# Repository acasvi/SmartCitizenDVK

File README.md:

Smart Citizen Kit DVK
=====================

**[Smart Citizen Kit](https://github.com/fablabbcn/Smart-Citizen-Kit) Develoment Kit (DVK) for [RTX4100](http://www.rtx.dk/RTX41xx_Wi-Fi_modules-3921.aspx) and [Arduino Due](http://arduino.cc/en/Main/arduinoBoardDue)**

*The Smart Citizen DVK is an Arduino Shield for the Arduino DUE and the upcoming Arduino Zero aimed to help developers prototype applications for the new Smart Citizen Kit Data Board 2.0. It contains a RTX4100 low-power Wi-Fi module, an SD card socket and a digital temperature and humidity sensor.*

## First Steps

### Installing the toolchain

The tool chain includes primarily a pre-processor, a compiler, and a linker. The RTX41xx relies on the GCC ARM Embedded tool chain from ARM.

Prior to installation, download the GNU tools for ARM embedded processors installation file from: https://launchpad.net/gcc-arm-embedded/+milestone/4.7-2013-q3-update

Download the `gcc-arm-none-eabi-4_7-2013q3-20130916-win32.exe` file, save to disk and run the `.exe` file. 

Don't forget to click “Add path to environment variable” checkbox at the end of the installation.

Refer to **[RTX4100_User_Guide_Tools_Installation_UG2.pdf](https://github.com/fablabbcn/SmartCitizenDVK/blob/master/Documentation/RTX4100/RTX4100_User_Guide_Tools_Installation_UG2.pdf)** for a further explanation about installation the toolchain and SDK.

### Installing the SDK

After installing the Tool Chain, it is time to install the RTX41xx Software Development Kit (SDK). 

Go to the following link: [www.rtx.dk/LPW/RTX4100](http://www.rtx.dk/LPW/RTX4100) and click on **DOWNLOAD** link on top right.

You have to sign up to download the latest SDK `AmelieSdk_v1.6.0.58.exe`.

Once you have downloaded open the `.exe` to start the installer.

The SDK download from RTX includes the following items:

* Sample code implementing the following applications: 
    * Blinky: Small example application that uses a timer to flash a LED on the demo board.
    * TCP Server/client
    * UDP Server/client
    * Terminal Application
    * 3 different Temperature Sensor implementations, demonstrating various low power capabilities.
    * TempSensorSoftApCfg, demonstrating how it is possible to configure a module by booting it in SoftAP mode with telnet support.
    * SoftApTcpServer, demonstrating an AP implementation with TCP server.
    * WebServer, demonstrating a very simple WEB server implementation.
    * Tcp2Uart, demonstrates a simple implementation of a data pipe
    * Cloud reference applications, demonstrating various cloud solutions 
    * Header files for available APIs.
    * Build environment: Build scripts, linker files etc. are provided for ARM GCC Em-bedded tool chain.
    * RTX EAI Port Server: PC application used for communicating with the hardware.
    * CoLA Controller DLL: Used for selecting active image and updating firmware.
    * CoLA Controller GUI: Example application using the DLL. In the end product the DLL could be used directly from e.g. an Eclipse IDE.

It is assumed that the SDK has been installed in c:\AmelieSdk\vX.XX, and the following description of the folder structure is relative to this location.

The following folders are at top level: 

* **3Party** – includes source files from 3rd parties. The most important file found here is the “efm32lib” from Energy Micro which is used to access the peripherals of the MCU.
* **ColaController** – The PC tool used to download Co-Located Applications to the module via the UART.
* **Components** – Source code to some common components used when the CoLA is built.
* **Documents** – Documentation folder.
* **Include** – Common header files.
* **Projects** – This is where you find the reference CoLA applications
* **Tools** – A set of tools used when the CoLA is built. This also includes the RtxBuild system used for the build process.

In the Project folder (Projects\Amelie\COLApps) you find the following folders:

* **Apps** – A set of reference applications 
	* Blinky – The source code for the Blinky application
	* Blinky/Build/RTX4100_WSAB – Build folder for RTX4100 module on WSAB.
	* Blinky/Build/RTX4140_WSAB – Build folder for RTX4140 module on WSAB.
* **Config** – This folder holds various configuration header files required to build the reference applications.
* **Rsx** – PC tool for API mail trace via UART.
* **Scripts** – build/linker scripts.

In the Components folder (Projects\Amelie\Componets) you find the following folders: 

* **Api** – Some API header files
* **ApiMps** – API mail packing and sending helper functions
* **Drivers** – Implementation of various hardware drivers 
* **PtApps** – Protothread based application framework used by all reference applica-tions except Blinky. 

Refer to **[RTX4100_User_Guide_Tools_Installation_UG2.pdf](https://github.com/fablabbcn/SmartCitizenDVK/blob/master/Documentation/RTX4100/RTX4100_User_Guide_Tools_Installation_UG2.pdf)** for a further explanation about installation the toolchain and SDK.

#### Application Development

For start with the **application development** refer to chapter 4 on [RTX4100_User_Guide_Application_Development_UG3.pdf](https://github.com/fablabbcn/SmartCitizenDVK/blob/master/Documentation/RTX4100/RTX4100_User_Guide_Application_Development_UG3.pdf)

For **terminal commands to configure WIFI** module refer to chapter 5 on [RTX4100_User_Guide_Module_Evaluation_UG1.pdf](https://github.com/fablabbcn/SmartCitizenDVK/blob/master/Documentation/RTX4100/RTX4100_User_Guide_Application_Development_UG3.pdf)

For **API used to program Co-Located Applications (CoLA)** on top of the Amelie Wi-Fi platform refer to [AmelieApi_V0106_N0052.pdf](https://github.com/fablabbcn/SmartCitizenDVK/blob/master/Documentation/RTX4100/AmelieApi_V0106_N0052.pdf)

## Software

All the boards come with:

* Arduino firmware *[SmartCitizen_DVK.ino](https://github.com/fablabbcn/SmartCitizenDVK/tree/master/Firmware)* uploaded. 
* RTX firmware uploaded
* CoLA application for terminal communication with WIFI module uploaded, for available **terminal commands** refer to chapter 5 on *[RTX4100_User_Guide_Module_Evaluation_UG1.pdf](https://github.com/fablabbcn/SmartCitizenDVK/blob/master/Documentation/RTX4100/RTX4100_User_Guide_Module_Evaluation_UG1.pdf)*

To use the RTX Shield connect an usb cable in the programming port of the Arduino Due, the one closest to the DC power jack.

As you can see, the RTX shield has two push buttons, **S1** and **S2**. With this two buttons you can change between 4 modes of operation:

####MODE 1

This is the default mode when you connect the board, green LED is ON. This mode sendsthrough USB-Serial, at 9600 bauds, the values captured by the temperature and humidity sensors and tells you if a SD Card is detected or not. You can find this values in the `main()` function of `SmartCitizen_DVK.ino`.

####MODE 2

If **S1** button is pushed, the green LED starts to blinking. You are on terminal mode. If a CoLa app for terminal communication is uploaded, yelllow LED ON, you can talk through USB-serial with the RTX WIFI module. If you push again S1, you'll go back to **MODE 1**.

####MODE 3

If **S2** button is pushed ,the blue LED goes ON, you can now upload CoLA applications with **ColaController**, the PC tool used to download Co-Located Applications to the module via the UART. You can find this tool on **ColaController** folder inside **Amelie SDK** folder.

####MODE 4

If **S2** button is pushed again, the green and blue LEDs goes ON, you will enter in RTX firmware uploading mode and the blue LED will start blinking.

To perform the Firmware update:

1. Download the firmware file **RTX41xx_Platform_Firmware_Update_Pack_v1.6.0.52.zip** from the RTX [download center](http://www.rtx.dk/Download_Center_Login-3980.aspx). 
2. Unzip the file to your harddrive. As this document is included in the above ZIP file you have probably already downloaded the file.

*NOTE: Each time you plug the arduino due with the shield to your computer automatically reses the mode to mode 1.*

### Existing software

* [Smart Citizen Kit firmware](https://github.com/fablabbcn/Smart-Citizen-Kit) for the Ambient Sensor Board 1.0-1.2 *(MCU ATMEGA32U4)*
* [Smart Citizen Kit RTX4100 Application - BETA](https://github.com/fablabbcn/SmartCitizenRTX4100)

## Hardware

SmartCitizen DVK shield design files are available [here](https://github.com/fablabbcn/SmartCitizenDVK/hardware).

### RTX4100 - Low power wifi module

* [http://www.rtx.dk/RTX41xx_Wi-Fi_modules-3921.aspx](http://www.rtx.dk/RTX41xx_Wi-Fi_modules-3921.aspx)

* [http://www.rtx.dk/Wi-Fi_Documentation-4028.aspx](http://www.rtx.dk/Wi-Fi_Documentation-4028.aspx)

The RTX41xx Wi-Fi Module is a low power solution, which is achieved through the use of the  Energy Micro Gecko and Atheros AR4100 Wi-Fi SiP.

**The I/O's include:**

* Power supply pins
* ADC ports, DAC ports
* GPIO ports
* UART, SPI, I2C
* Timers

#### NC7SZ157P6X – MUX

[http://www.mouser.com/ds/2/149/NC7SZ157-96268.pdf](http://www.mouser.com/ds/2/149/NC7SZ157-96268.pdf)

The mux is used to select from Arduino which serial port of the RTX4100 you want to use.

You can select between two serial ports:

* **LEU1**: (LEUART) is used for the Terminal application (such at Putty), for example.
* **US1**: (USART) is used for the COLApp loading, SW debugging and Platform updates (using the COLApp Controller)

#### MCP1725-3002E/SN LDO REGULATOR

[http://ww1.microchip.com/downloads/en/DeviceDoc/22026b.pdf](%22http:)

3V fixed voltage regulator

#### CD74HC4050M High-to-Low Voltage Level Converter

[http://www.mouser.com/ds/2/405/schs205i-101882.pdf](http://www.mouser.com/ds/2/405/schs205i-101882.p)

IC used as logic level converter between Arduino and the RTX4100 module.

#### SDCARD

[http://www.mouser.com/ds/2/185/e60900232-38395.pdf](http://www.mouser.com/ds/2/185/e60900232-38395.pdf)

To hold the SD card we are using the DM3CS holder. The SD card is powered at 3V and communicates with the RTX4100 through SPI protocol.

#### SHT21 Humidity and Temperature Sensor IC

[http://www.sensirion.com/fileadmin/user_upload/customers/sensirion/Dokumente/Humidity/Sensirion_Humidity_SHT21_Datasheet_V4.pdf](http://www.sensirion.com/fileadmin/user_upload/customers/s)

#### LEDs

* **LED1 YELLOW:** Connected to RTX4100 pin 27, for testing Blink CoLA example
* **LED2 BLUE:** Connected to Arduino Analog0 pin
* **LED3 GREEN:** Connected to Arduino Analog1 pin

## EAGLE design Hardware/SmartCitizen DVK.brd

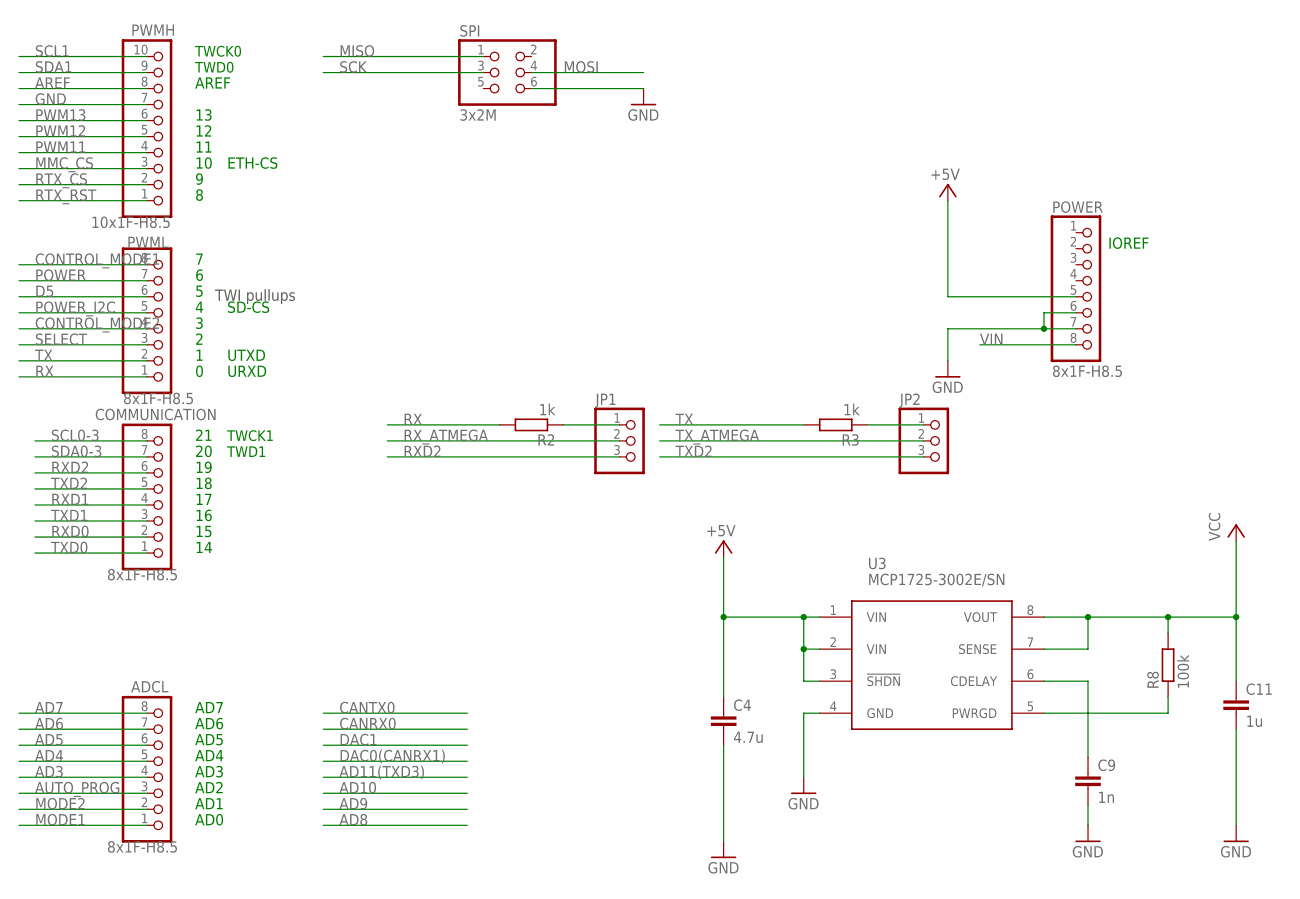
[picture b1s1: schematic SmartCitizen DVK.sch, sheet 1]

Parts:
ADCL: 8x1F-H8.5; 1X08
C4: 4.7u; C0805
C9: 1n; C0805
C11: 1u; C0805
COMMUNICATION: 8x1F-H8.5; 1X08
JP1, JP2: PINHD-1X3; 1X03
POWER: 8x1F-H8.5; 1X08
PWMH: 10x1F-H8.5; 1X10
PWML: 8x1F-H8.5; 1X08
R2, R3: 1k; R0805
R8: 100k; R0805
SPI: 3x2M; 2X03
U3: MCP1725-3002E/SN; SOIC8

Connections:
+5V: C4.1, POWER.5, U3.1 (VIN), U3.2 (VIN), U3.3 (!SHDN); also elsewhere on the board
AD3: ADCL.4
AD4: ADCL.5
AD5: ADCL.6
AD6: ADCL.7
AD7: ADCL.8
AREF: PWMH.8
AUTO_PROG: ADCL.3; also elsewhere on the board
CONTROL_MODE1: PWML.8; also elsewhere on the board
CONTROL_MODE2: PWML.4; also elsewhere on the board
D5: PWML.6
GND: C4.2, C9.2, C11.2, POWER.6, POWER.7, PWMH.7, SPI.6, U3.4 (GND); also elsewhere on the board
MISO: SPI.1; also elsewhere on the board
MMC_CS: PWMH.3; also elsewhere on the board
MODE1: ADCL.1; also elsewhere on the board
MODE2: ADCL.2; also elsewhere on the board
MOSI: SPI.4; also elsewhere on the board
unnamed: JP1.1, R2.1
unnamed: JP2.1, R3.1
unnamed: C9.1, U3.6 (CDELAY)
unnamed: R8.1, U3.5 (PWRGD)
POWER: PWML.7; also elsewhere on the board
POWER_I2C: PWML.5; also elsewhere on the board
PWM11: PWMH.4
PWM12: PWMH.5
PWM13: PWMH.6
RTX_CS: PWMH.2; also elsewhere on the board
RTX_RST: PWMH.1; also elsewhere on the board
RX: PWML.1, R2.2
RXD0: COMMUNICATION.2
RXD1: COMMUNICATION.4
RXD2: COMMUNICATION.6, JP1.3
RX_ATMEGA: JP1.2; also elsewhere on the board
SCK: SPI.3; also elsewhere on the board
SCL0-3: COMMUNICATION.8
SCL1: PWMH.10; also elsewhere on the board
SDA0-3: COMMUNICATION.7
SDA1: PWMH.9; also elsewhere on the board
SELECT: PWML.3; also elsewhere on the board
TX: PWML.2, R3.2
TXD0: COMMUNICATION.1
TXD1: COMMUNICATION.3
TXD2: COMMUNICATION.5, JP2.3
TX_ATMEGA: JP2.2; also elsewhere on the board
VCC: C11.1, R8.2, U3.7 (SENSE), U3.8 (VOUT); also elsewhere on the board
VIN: POWER.8

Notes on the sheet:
TWI pullups
TWCK1
TWD1
IOREF
TWCK0
TWD0
AD1
AD2
AD3
AD4
AD5
AD6
AD0
AREF
AD7
SD-CS
UTXD
URXD
ETH-CS

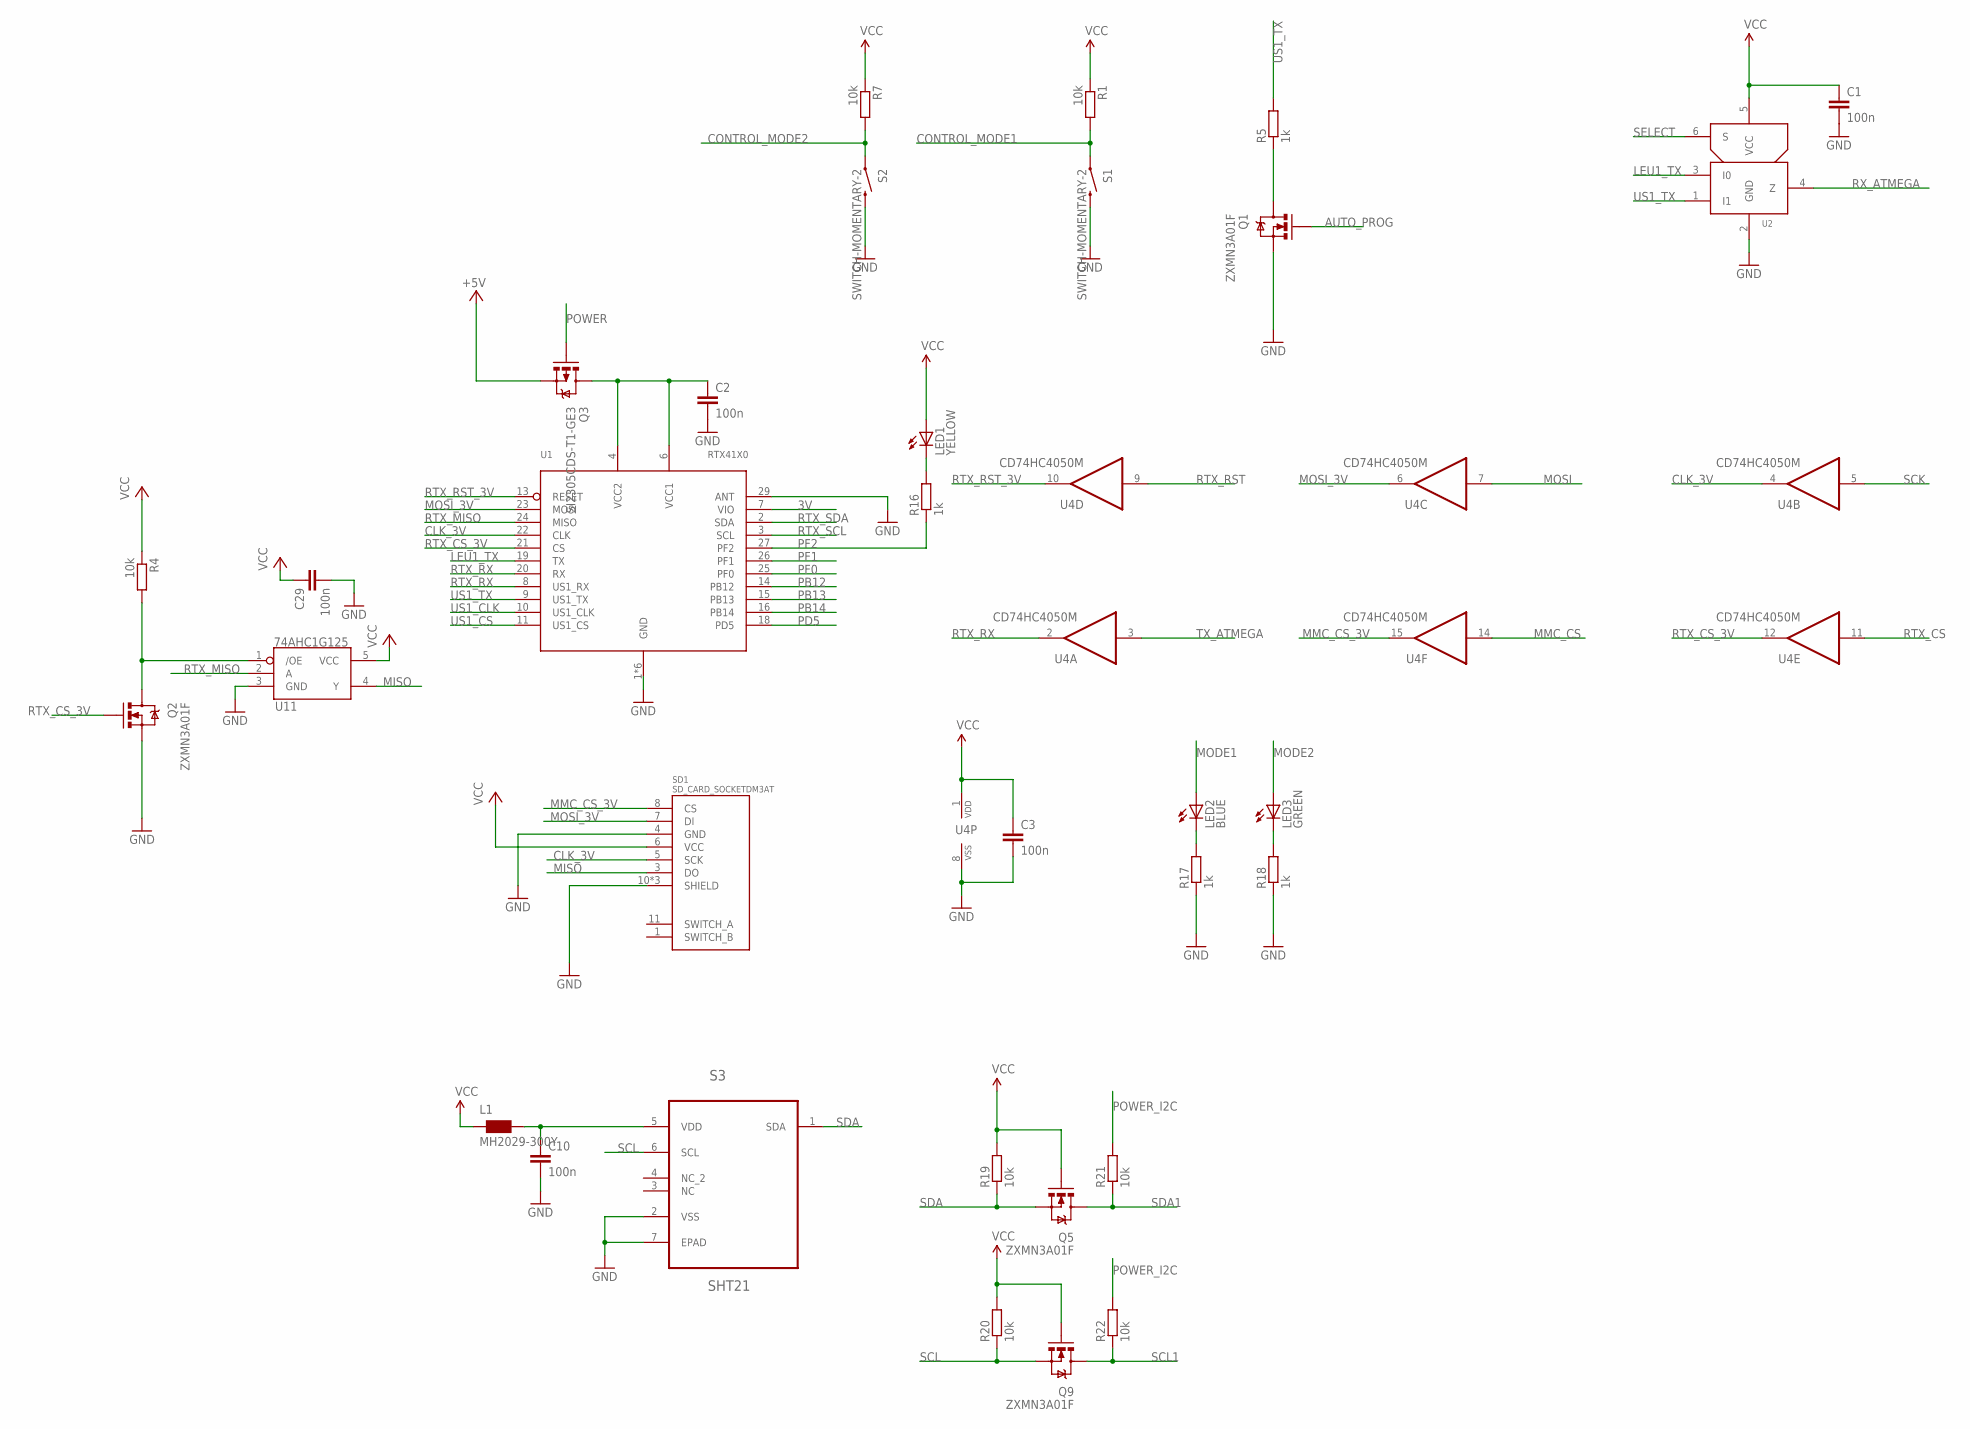
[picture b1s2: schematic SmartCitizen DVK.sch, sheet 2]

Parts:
C1, C2, C3, C10, C29: 100n; C0805
L1: MH2029-300Y; 0805
LED1: YELLOW; CHIPLED_0805
LED2: BLUE; CHIPLED_0805
LED3: GREEN; CHIPLED_0805
Q1, Q2, Q5, Q9: ZXMN3A01F; SOT23
Q3: SI2305CDS-T1-GE3; SOT23-3
R1, R4, R7, R19, R20, R21, R22: 10k; R0805
R5, R16, R17, R18: 1k; R0805
S1, S2: SWITCH-MOMENTARY-2; TACTILE_SWITCH_TALL
S3: SHT21; DFN300X300X110-7N
SD1: SD_CARD_SOCKETDM3AT; DM3AT
U1: RTX41X0
U2: NC7SZ157P6X; SC70
U4: CD74HC4050M; SO16
U11: 74AHC1G125; SOT23-5

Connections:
3V: U1.7 (VIO)
+5V: Q3.2 (S); also elsewhere on the board
AUTO_PROG: Q1.1 (G); also elsewhere on the board
CLK_3V: SD1.5 (SCK), U1.22 (CLK), U4.4 (O)
CONTROL_MODE1: R1.2, S1.A2 (1); also elsewhere on the board
CONTROL_MODE2: R7.2, S2.A2 (1); also elsewhere on the board
GND: C1.2, C2.2, C3.2, C10.2, C29.2, Q1.2 (S), Q2.2 (S), R17.1, R18.1, S1.B2 (2), S2.B2 (2), S3.2 (VSS), S3.7 (EPAD), SD1.4 (GND), SD1.10 (SHIELD), SD1.12 (SHIELD), SD1.13 (SHIELD), U1.1 (GND), U1.5 (GND), U1.12 (GND), U1.17 (GND), U1.28 (GND), U1.29 (ANT), U1.30 (GND), U2.2 (GND), U4.8 (VSS), U11.3 (GND); also elsewhere on the board
LEU1_TX: U1.19 (TX), U2.3 (I0)
MISO: SD1.3 (DO), U11.4 (Y); also elsewhere on the board
MMC_CS: U4.14 (I); also elsewhere on the board
MMC_CS_3V: SD1.8 (CS), U4.15 (O)
MODE1: LED2.A; also elsewhere on the board
MODE2: LED3.A; also elsewhere on the board
MOSI: U4.7 (I); also elsewhere on the board
MOSI_3V: SD1.7 (DI), U1.23 (MOSI), U4.6 (O)
unnamed: Q1.3 (D), R5.1
unnamed: LED1.C, R16.2
unnamed: LED2.C, R17.2
unnamed: LED3.C, R18.2
unnamed: C10.1, L1.2, S3.5 (VDD)
unnamed: Q2.3 (D), R4.2, U11.1 (/OE)
PB12: U1.14 (PB12)
PB13: U1.15 (PB13)
PB14: U1.16 (PB14)
PD5: U1.18 (PD5)
PF0: U1.25 (PF0)
PF1: U1.26 (PF1)
PF2: R16.1, U1.27 (PF2)
POWER: Q3.1 (G); also elsewhere on the board
POWER_I2C: R21.2, R22.2; also elsewhere on the board
RTX_CS: U4.11 (I); also elsewhere on the board
RTX_CS_3V: Q2.1 (G), U1.21 (CS), U4.12 (O)
RTX_MISO: U1.24 (MISO), U11.2 (A)
RTX_RST: U4.9 (I); also elsewhere on the board
RTX_RST_3V: U1.13 (RESET), U4.10 (O)
RTX_RX: U1.8 (US1_RX), U1.20 (RX), U4.2 (O)
RTX_SCL: U1.3 (SCL)
RTX_SDA: U1.2 (SDA)
RX_ATMEGA: U2.4 (Z); also elsewhere on the board
SCK: U4.5 (I); also elsewhere on the board
SCL: Q9.2 (S), R20.1, S3.6 (SCL)
SCL1: Q9.3 (D), R22.1; also elsewhere on the board
SDA: Q5.2 (S), R19.1, S3.1 (SDA)
SDA1: Q5.3 (D), R21.1; also elsewhere on the board
SELECT: U2.6 (S); also elsewhere on the board
TX_ATMEGA: U4.3 (I); also elsewhere on the board
US1_CLK: U1.10 (US1_CLK)
US1_CS: U1.11 (US1_CS)
US1_TX: R5.2, U1.9 (US1_TX), U2.1 (I1)
VCC: C1.1, C3.1, C29.1, L1.1, LED1.A, Q5.1 (G), Q9.1 (G), R1.1, R4.1, R7.1, R19.2, R20.2, SD1.6 (VCC), U2.5 (VCC), U4.1 (VDD), U11.5 (VCC); also elsewhere on the board
VCC2: C2.1, Q3.3 (D), U1.4 (VCC2), U1.6 (VCC1)

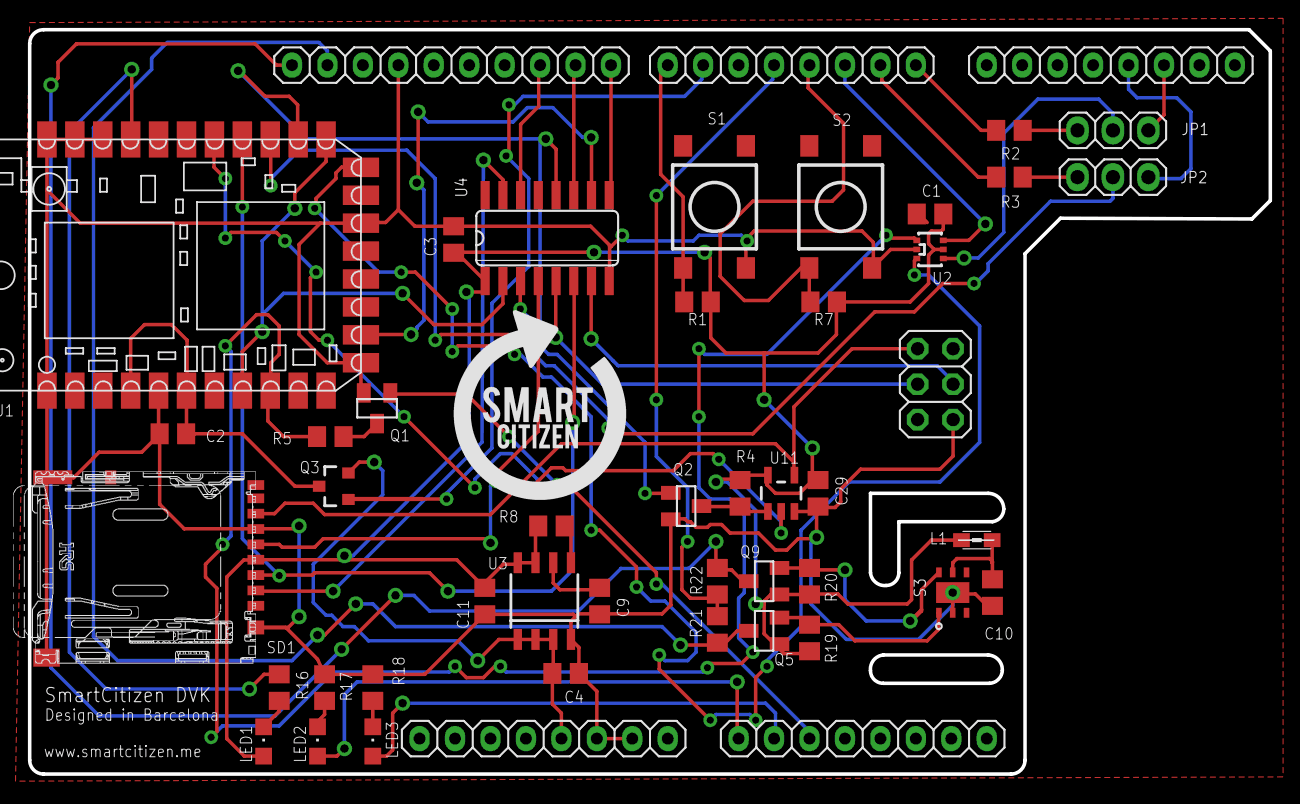
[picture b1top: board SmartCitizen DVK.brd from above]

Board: 2 copper layers, 88.9 x 53.3 mm, 48 parts (0 on the bottom side), 48 nets.

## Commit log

2015-04-15 Documentation
2015-04-15 Removed old files
2015-04-15 Documentation URLs
2015-04-15 Image CDN
2015-04-15 minor changes
2015-04-15 references
2015-04-16 Documentation details

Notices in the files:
parts and their libraries:
SparkFun-DiscreteSemi: Licensing: Creative Commons ShareAlike 4.0 International - https://creativecommons.org/licenses/by-sa/4.0
SparkFun-DigitalIC: Licensing: CC v3.0 Share-Alike You are welcome to use this library for commercial purposes.
